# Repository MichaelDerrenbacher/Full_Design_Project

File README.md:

# Full_Design_Project
Wide Voltage Input Microphone to LED Output

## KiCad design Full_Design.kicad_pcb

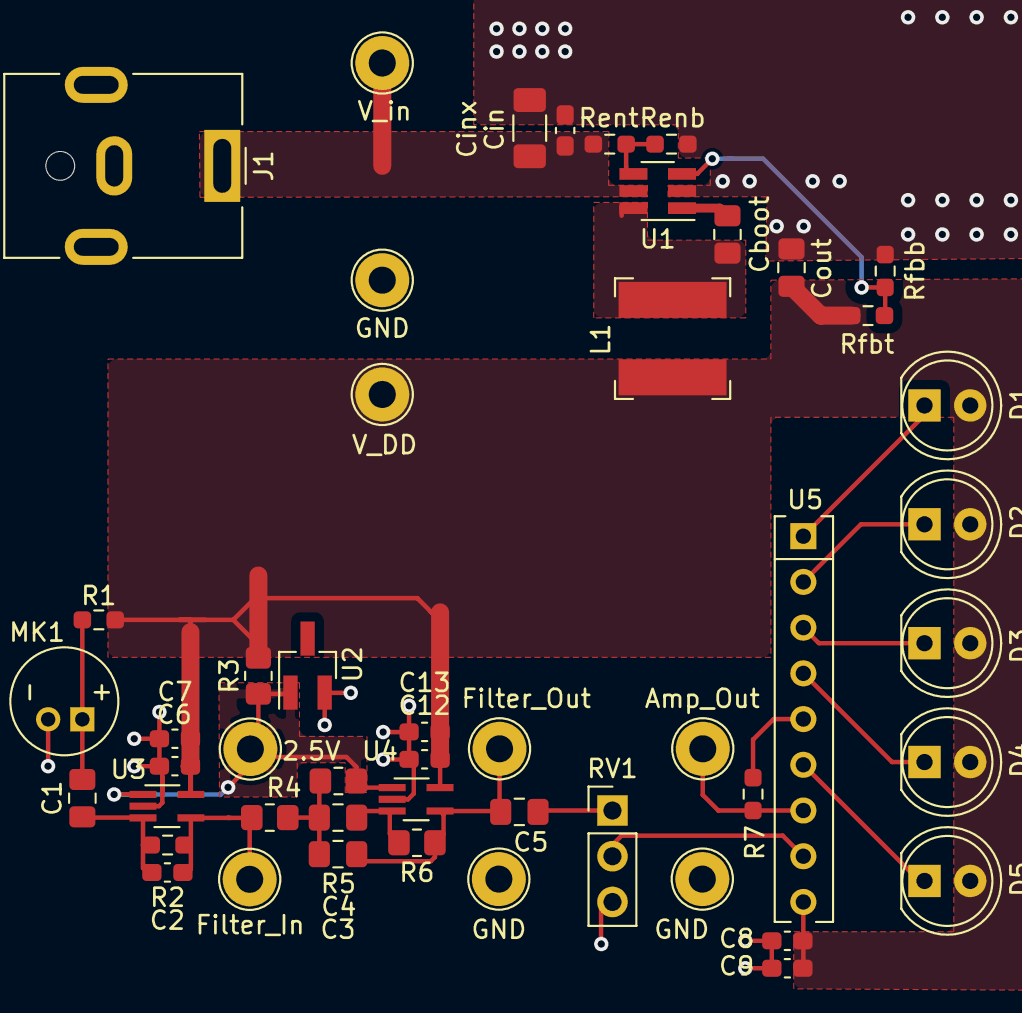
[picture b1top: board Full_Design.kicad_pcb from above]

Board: 2 copper layers, 49 parts (0 on the bottom side), 22 nets.

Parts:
2.5V: TestPoint; TestPoint_Loop_D2.54mm_Drill1.5mm_Beaded
Amp_Out: TestPoint; TestPoint_Loop_D2.54mm_Drill1.5mm_Beaded
C1, C5: 4.7u; C_0805_2012Metric_Pad1.18x1.45mm_HandSolder
C2: 18p; C_0603_1608Metric_Pad1.08x0.95mm_HandSolder
C3: 33n; C_0805_2012Metric_Pad1.18x1.45mm_HandSolder
C4: 47n; C_0805_2012Metric_Pad1.18x1.45mm_HandSolder
C6, C8, C12: 100n; C_0603_1608Metric_Pad1.08x0.95mm_HandSolder
C7, C9, C13: 1u; C_0603_1608Metric_Pad1.08x0.95mm_HandSolder
Cboot: 100n; C_0805_2012Metric_Pad1.18x1.45mm_HandSolder
Cin: 4.7u; C_1206_3216Metric_Pad1.33x1.80mm_HandSolder
Cinx: 100n; C_0603_1608Metric_Pad1.08x0.95mm_HandSolder
Cout: 15u; C_0805_2012Metric_Pad1.18x1.45mm_HandSolder
D1, D2, D3, D4, D5: LED; LED_D5.0mm
Filter_In: TestPoint; TestPoint_Loop_D2.54mm_Drill1.5mm_Beaded
Filter_Out: TestPoint; TestPoint_Loop_D2.54mm_Drill1.5mm_Beaded
GND: TestPoint; TestPoint_Loop_D2.54mm_Drill1.5mm_Beaded
GND#2, GND#3: TestPoint; TestPoint_Loop_D2.54mm_Drill1.5mm_Beaded
J1: Barrel_Jack; BarrelJack_CUI_PJ-063AH_Horizontal
L1: 39u; L_Bourns-SRN6045
MK1: Microphone; Microphone_P1.9mm
R1: 4.02k; R_0603_1608Metric_Pad0.98x0.95mm_HandSolder
R2: 68.1k; R_0603_1608Metric_Pad0.98x0.95mm_HandSolder
R3: 1k; R_0805_2012Metric_Pad1.20x1.40mm_HandSolder
R4: 4.7k; R_0805_2012Metric_Pad1.20x1.40mm_HandSolder
R5: 3.3k; R_0805_2012Metric_Pad1.20x1.40mm_HandSolder
R6: 8.2k; R_0805_2012Metric_Pad1.20x1.40mm_HandSolder
R7: 100k; R_0603_1608Metric_Pad0.98x0.95mm_HandSolder
RV1: 10k; PinHeader_1x03_P2.54mm_Vertical
Renb: 200k; R_0603_1608Metric_Pad0.98x0.95mm_HandSolder
Rent: 412k; R_0603_1608Metric_Pad0.98x0.95mm_HandSolder
Rfbb: 22.1k; R_0603_1608Metric_Pad0.98x0.95mm_HandSolder
Rfbt: 66.5k; R_0603_1608Metric_Pad0.98x0.95mm_HandSolder
U1: LMR50410; SOT-23-6_Handsoldering
U2: LM4040DBZ-2.5; SOT-23_Handsoldering
U3, U4: TLV9001IDCK; SOT-353_SC-70-5_Handsoldering
U5: AN6884; SIP-9_22.3x3mm_P2.54mm
V_DD: TestPoint; TestPoint_Loop_D2.54mm_Drill1.5mm_Beaded
V_in: TestPoint; TestPoint_Loop_D2.54mm_Drill1.5mm_Beaded

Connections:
0: C6.1, C7.1, C8.1, C9.1, C12.1, C13.1, Cin.1, Cinx.1, Cout.1, GND.1, GND#2.1, GND#3.1, J1.2, MK1.1, R7.2, RV1.3, Renb.2, Rfbb.2, U1.2, U2.2, U3.2, U4.2, U5.5
2.5V: 2.5V.1, R3.1, R5.2, U2.1, U3.1, U4.1
Filter_in: C2.1, Filter_In.1, R2.1, R4.2, U3.4
unnamed: C1.1, C2.2, R2.2, U3.3
unnamed: C1.2, MK1.2, R1.2
unnamed: C3.1, C4.2, R4.1, R5.1
unnamed: C4.1, R6.2, U4.3
unnamed: C5.1, RV1.1
unnamed: Cboot.1, L1.1, U1.6
unnamed: Cboot.2, U1.1
unnamed: D1.1, U5.1
unnamed: D2.1, U5.2
unnamed: D3.1, U5.3
unnamed: D4.1, U5.4
unnamed: D5.1, U5.6
unnamed: Amp_Out.1, R7.1, U5.7
unnamed: RV1.2, U5.8
unnamed: Renb.1, Rent.2, U1.4
unnamed: Rfbb.1, Rfbt.2, U1.3
V_DD: C6.2, C7.2, C8.2, C9.2, C12.2, C13.2, Cout.2, D1.2, D2.2, D3.2, D4.2, D5.2, L1.2, R1.1, R3.2, Rfbt.1, U3.5, U4.5, U5.9, V_DD.1
V_in: Cin.2, Cinx.2, J1.1, Rent.1, U1.5, V_in.1
filter_out: C3.2, C5.2, Filter_Out.1, R6.1, U4.4
